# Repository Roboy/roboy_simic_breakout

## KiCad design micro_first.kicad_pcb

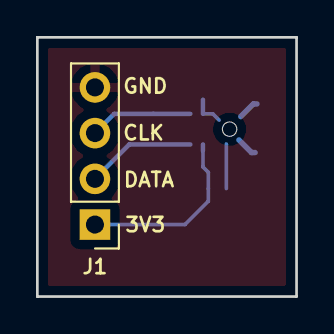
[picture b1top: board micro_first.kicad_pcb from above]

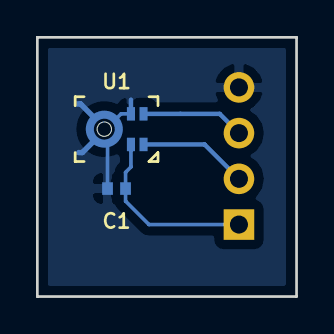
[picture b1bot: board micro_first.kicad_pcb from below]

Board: 2 copper layers, 14.4 x 14.4 mm, 3 parts (2 on the bottom side), 4 nets.

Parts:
C1: 100n; The_0402_FP
J1: Conn_01x04; PinHeader_1x04_P2.54mm_Vertical
U1: Simic_Infineon; IM69D130_Simic_uPhone

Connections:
+3V3: C1.1, J1.1, U1.2
/CLK: J1.3, U1.3
/DATA: J1.2, U1.1
GND: C1.2, J1.4, U1.4, U1.5

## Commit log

2018-06-06 First commit and already finished!
2018-06-15 Updated mic footprint and included some fixes to send the board to manufacturing.
